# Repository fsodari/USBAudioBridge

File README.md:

# USB Audio Bridge

KiCAD Project for a USB Audio Bridge based on an NXP RT1010

## Requirements

- NXP RT1010
- High Speed USB C connector
- MCU Link compatible SWD header
- 2 PMOD pin headers designed to mate with an Arty A7 development board
    - Route 2 I2S busses through one PMOD. One for input, one for output
    - Route SPI and GPIO through the second PMOD.
- Should be designed for a USB asynchronous audio class device.
- Should use a stable, accurate, 24.576Mhz oscillator for the Audio master clock

## KiCAD Project Requirements
- All erc/drc should pass
- Include 3D models for all parts
- Set up pipelines to generate design files that can be delivered to a PCBA manufacturer

## Using this repository

- `hardware/`: KiCad 10 project (revision v1.0). The schematic is generated from `tools/design.py`; edit that, not the `.kicad_sch` files.
- `docs/reference-manual.md`: developer reference for the RT1010 firmware and the Arty A7 FPGA design (pin map, clocks, boot, I2S/USB/SPI, XDC constraints, errata).
- Fabrication outputs for JLCPCB and PCBWay (Gerbers, drill, BOM, pick-and-place, assembly drawings, schematic PDF):
  - locally: `python3 tools/fab.py` (needs KiCad 10), output in `hardware/build/fab/`
  - on GitHub: the "Fabrication outputs" workflow runs on every push to `main` and uploads both packages as artifacts; pushing a `v*` tag attaches them to a release.

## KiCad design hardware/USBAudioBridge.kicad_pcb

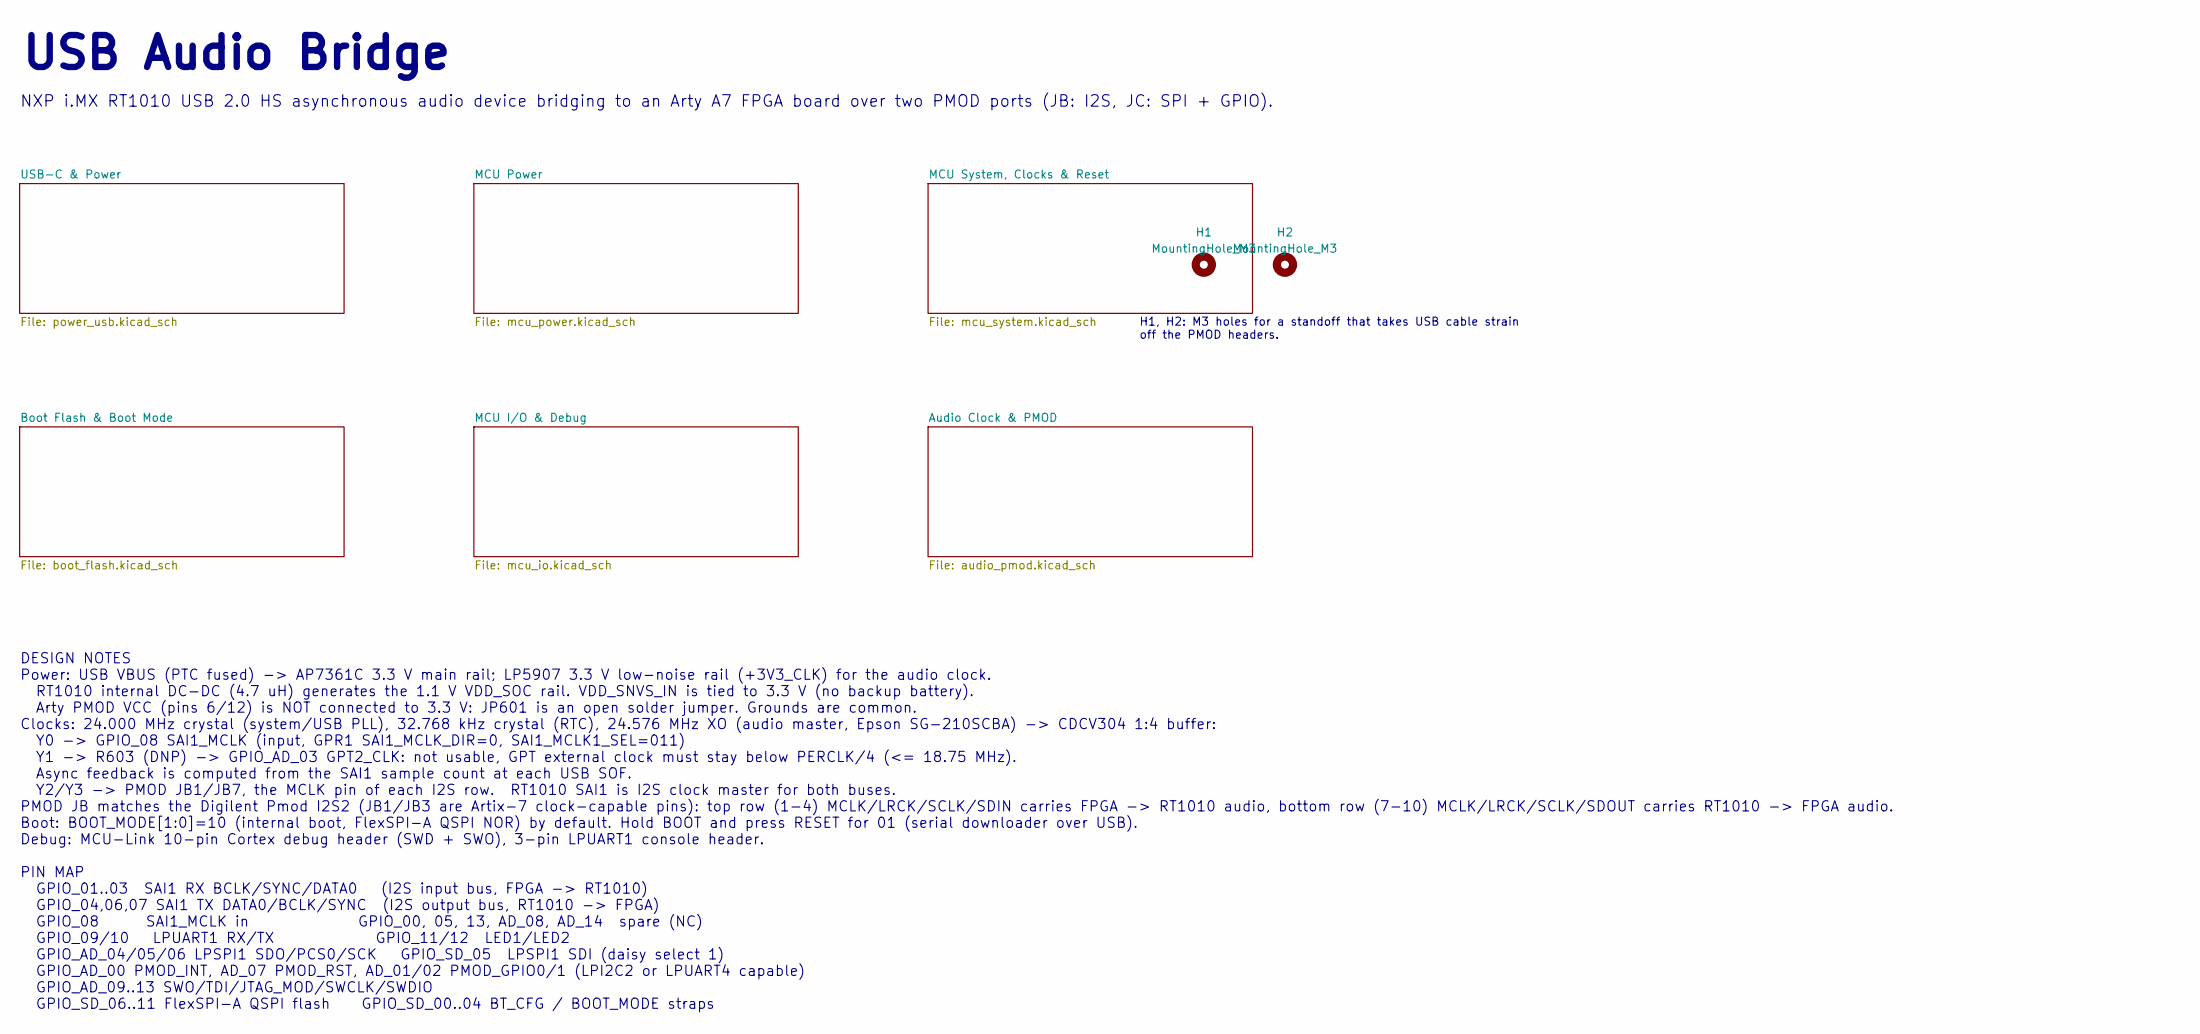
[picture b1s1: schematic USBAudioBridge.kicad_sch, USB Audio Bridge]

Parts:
H1, H2: MountingHole_M3; MountingHole_3.2mm_M3

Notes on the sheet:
USB Audio Bridge
DESIGN NOTES Power: USB VBUS (PTC fused) -> AP7361C 3.3 V main rail; LP5907 3.3 V low-noise rail (+3V3_CLK) for the audio clock. RT1010 internal DC-DC (4.7 uH) generates the 1.1 V VDD_SOC rail. VDD_SNVS_IN is tied to 3.3 V (no backup battery). Arty PMOD VCC (pins 6/12) is NOT connected to 3.3 V: JP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
H1, H2: M3 holes for a standoff that takes USB cable strain off the PMOD headers.
NXP i.MX RT1010 USB 2.0 HS asynchronous audio device bridging to an Arty A7 FPGA board over two PMOD ports (JB: I2S, JC: SPI + GPIO).

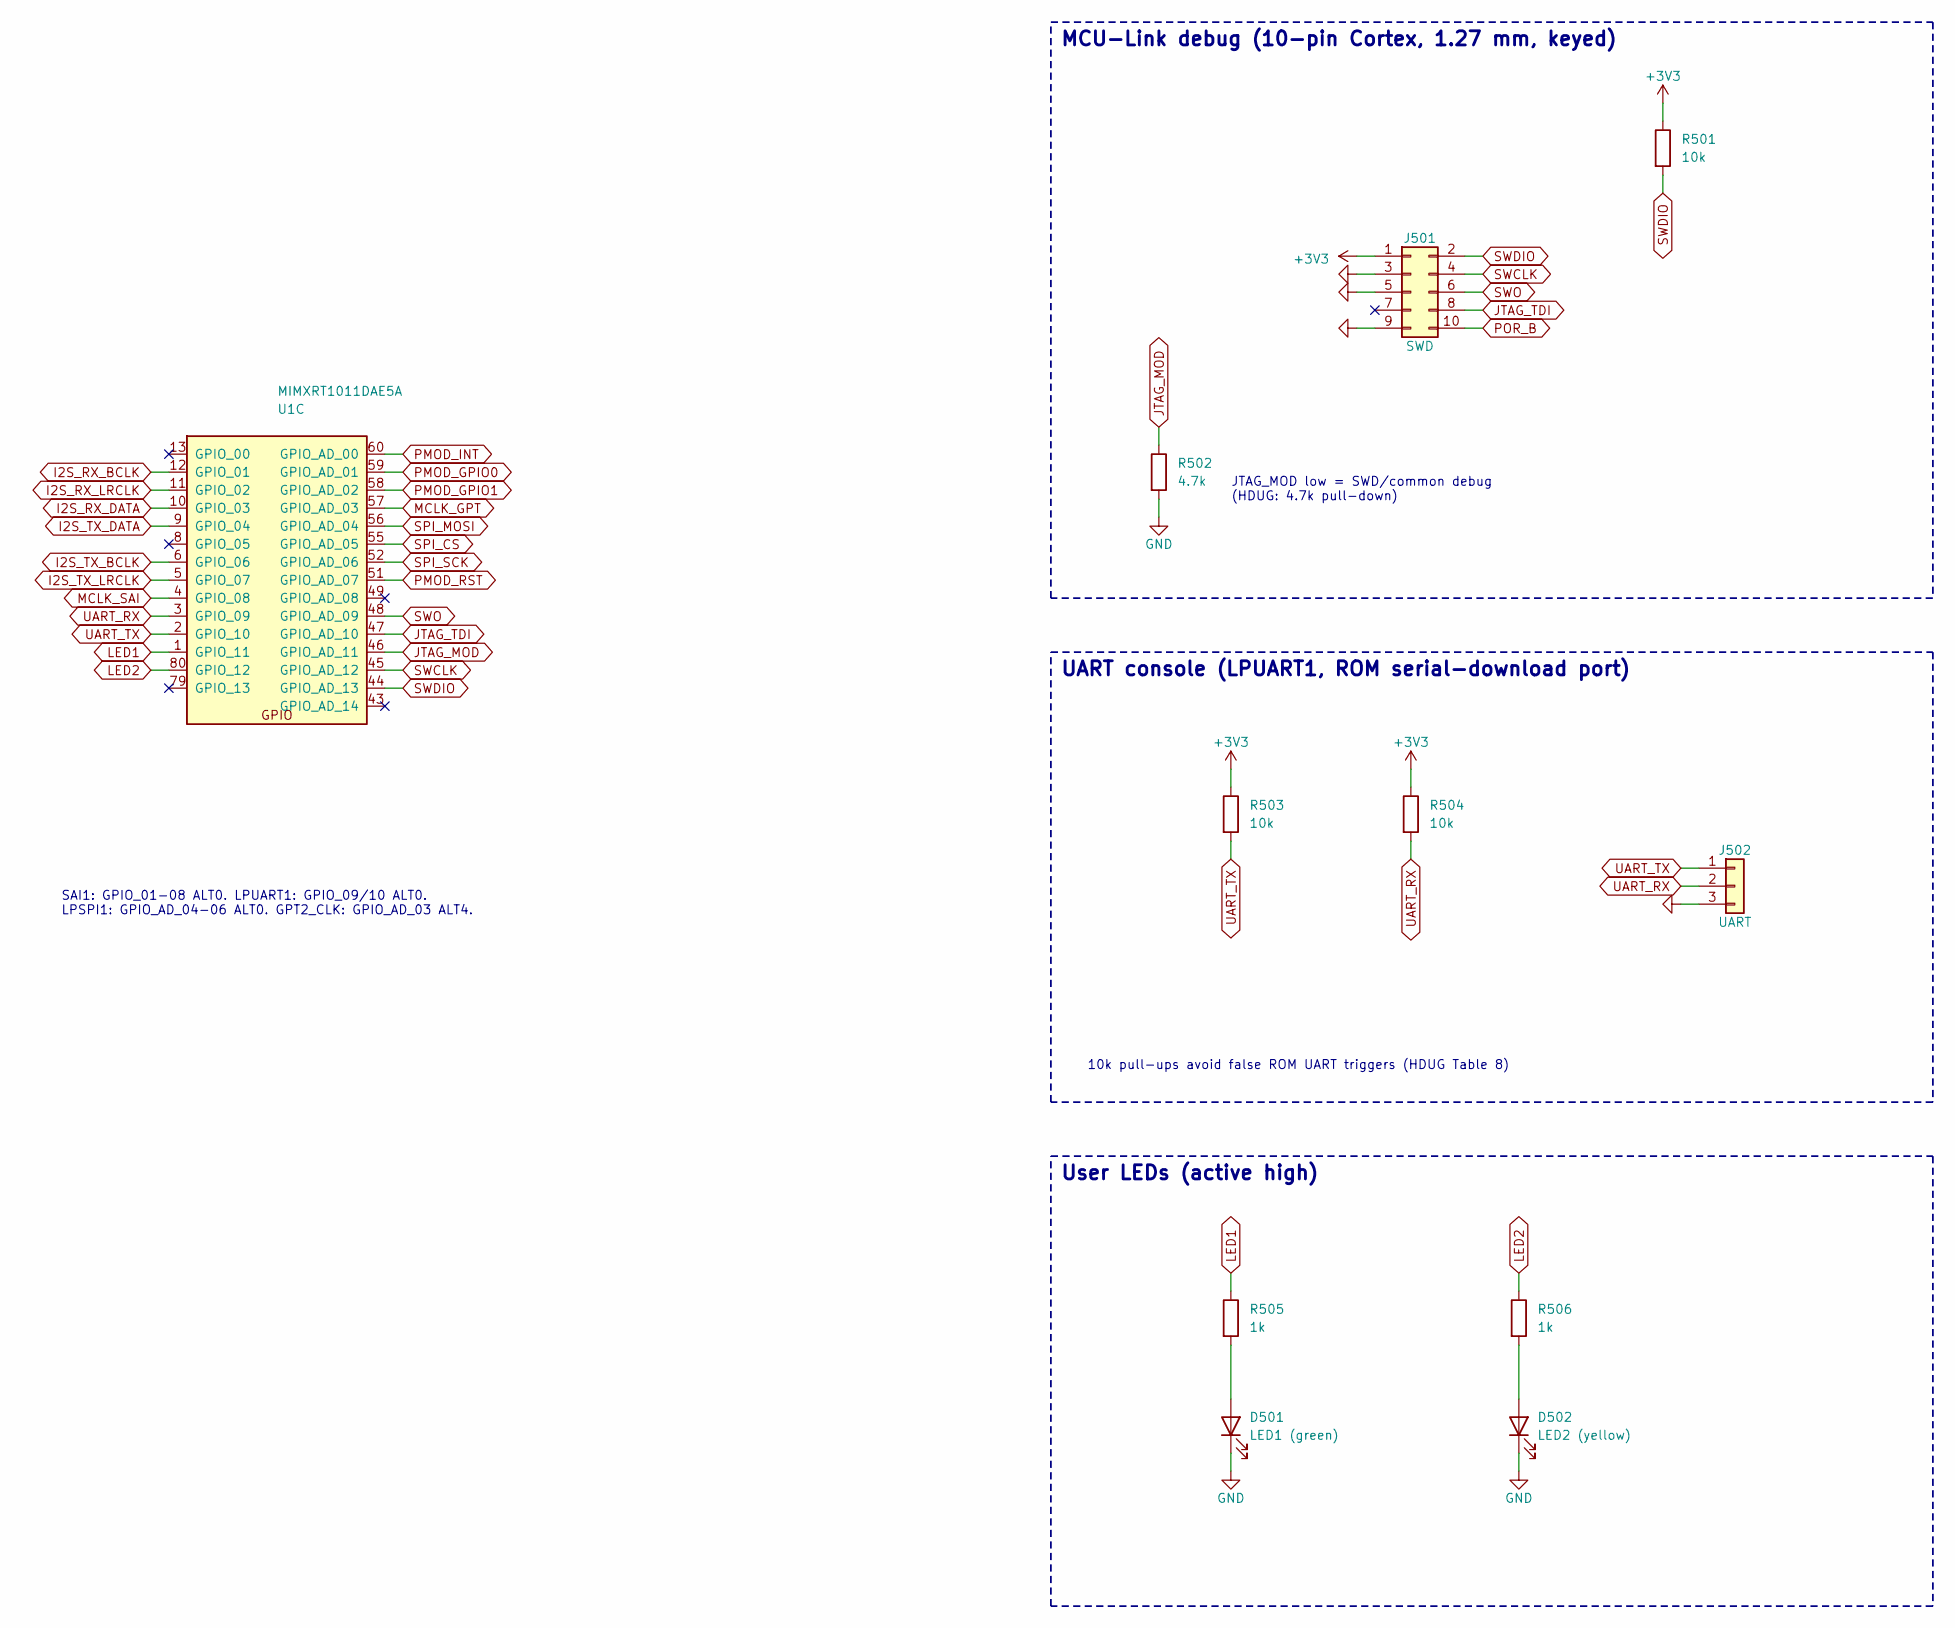
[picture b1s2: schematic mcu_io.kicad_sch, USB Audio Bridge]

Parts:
D501: LED1 (green); LED_0603_1608Metric; MPN KT-0603YG; LCSC C2289
D502: LED2 (yellow); LED_0603_1608Metric; MPN KT-0603Y; LCSC C2287
J501: SWD; Samtec_FTSH-105-01-L-DV-K; MPN FTSH-105-01-L-DV-K; LCSC C5155080
J502: UART; PinHeader_1x03_P2.54mm_Vertical; MPN PZ254V-11-03P; LCSC C2937625
R501, R503, R504: 10k; R_0402_1005Metric; MPN 0402WGF1002TCE; LCSC C25744
R502: 4.7k; R_0402_1005Metric; MPN 0402WGF4701TCE; LCSC C25900
R505, R506: 1k; R_0402_1005Metric; MPN 0402WGF1001TCE; LCSC C11702
U1: MIMXRT1011DAE5A; LQFP-80_12x12mm_P0.5mm; MPN MIMXRT1011DAE5A; LCSC C1575810

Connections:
+3V3: J501.1, R501.1, R503.1, R504.1; also elsewhere on the board
GND: D501.1 (K), D502.1 (K), J501.3, J501.5, J501.9, J502.3, R502.2; also elsewhere on the board
I2S_RX_BCLK: U1.12 (GPIO_01); also elsewhere on the board
I2S_RX_DATA: U1.10 (GPIO_03); also elsewhere on the board
I2S_RX_LRCLK: U1.11 (GPIO_02); also elsewhere on the board
I2S_TX_BCLK: U1.6 (GPIO_06); also elsewhere on the board
I2S_TX_DATA: U1.9 (GPIO_04); also elsewhere on the board
I2S_TX_LRCLK: U1.5 (GPIO_07); also elsewhere on the board
JTAG_MOD: R502.1, U1.46 (GPIO_AD_11)
JTAG_TDI: J501.8, U1.47 (GPIO_AD_10)
LED1: R505.1, U1.1 (GPIO_11)
LED2: R506.1, U1.80 (GPIO_12)
MCLK_GPT: U1.57 (GPIO_AD_03); also elsewhere on the board
MCLK_SAI: U1.4 (GPIO_08); also elsewhere on the board
unnamed: D501.2 (A), R505.2
unnamed: D502.2 (A), R506.2
PMOD_GPIO0: U1.59 (GPIO_AD_01); also elsewhere on the board
PMOD_GPIO1: U1.58 (GPIO_AD_02); also elsewhere on the board
PMOD_INT: U1.60 (GPIO_AD_00); also elsewhere on the board
PMOD_RST: U1.51 (GPIO_AD_07); also elsewhere on the board
POR_B: J501.10; also elsewhere on the board
SPI_CS: U1.55 (GPIO_AD_05); also elsewhere on the board
SPI_MOSI: U1.56 (GPIO_AD_04); also elsewhere on the board
SPI_SCK: U1.52 (GPIO_AD_06); also elsewhere on the board
SWCLK: J501.4, U1.45 (GPIO_AD_12)
SWDIO: J501.2, R501.2, U1.44 (GPIO_AD_13)
SWO: J501.6, U1.48 (GPIO_AD_09)
UART_RX: J502.2, R504.2, U1.3 (GPIO_09)
UART_TX: J502.1, R503.2, U1.2 (GPIO_10)

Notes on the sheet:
10k pull-ups avoid false ROM UART triggers (HDUG Table 8)
UART console (LPUART1, ROM serial-download port)
User LEDs (active high)
SAI1: GPIO_01-08 ALT0. LPUART1: GPIO_09/10 ALT0. LPSPI1: GPIO_AD_04-06 ALT0. GPT2_CLK: GPIO_AD_03 ALT4.
MCU-Link debug (10-pin Cortex, 1.27 mm, keyed)
JTAG_MOD low = SWD/common debug (HDUG: 4.7k pull-down)

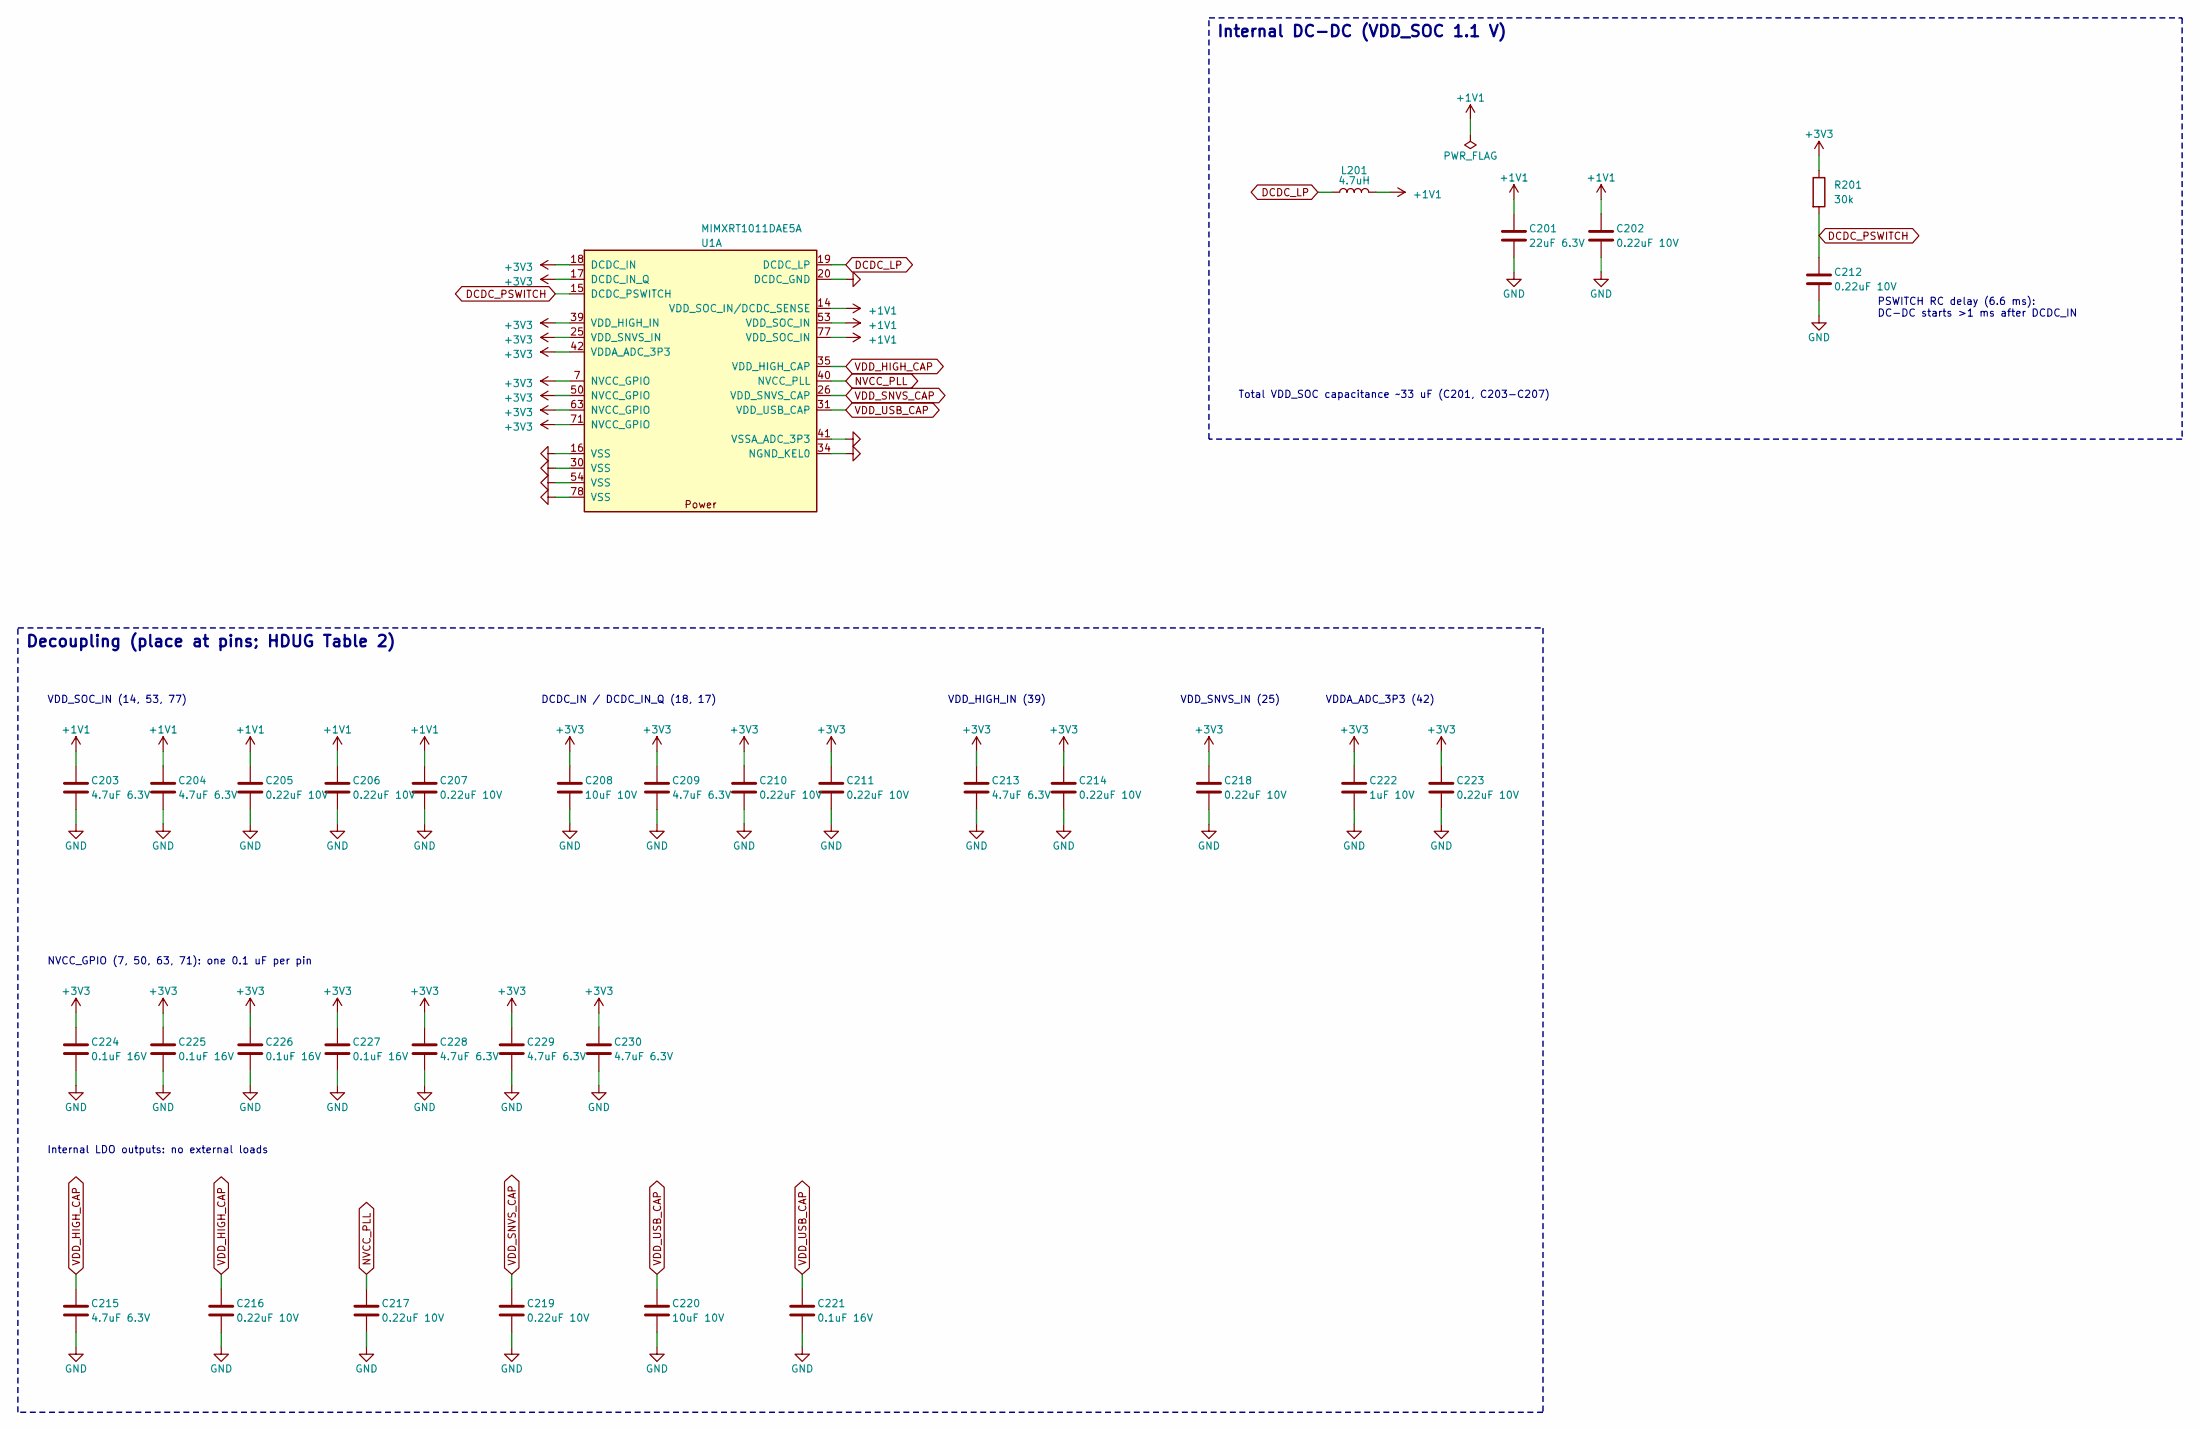
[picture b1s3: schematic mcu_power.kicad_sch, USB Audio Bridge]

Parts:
C201: 22uF 6.3V; C_0805_2012Metric; MPN CL21A226MAQNNNE; LCSC C45783
C202, C205, C206, C207, C210, C211, C212, C214, C216, C217, C218, C219, C223: 0.22uF 10V; C_0402_1005Metric; MPN CL05B224KO5NNNC; LCSC C16772
C203, C204, C209, C213, C215, C228, C229, C230: 4.7uF 6.3V; C_0402_1005Metric; MPN CL05A475MP5NRNC; LCSC C23733
C208, C220: 10uF 10V; C_0603_1608Metric; MPN CL10A106KP8NNNC; LCSC C19702
C221, C224, C225, C226, C227: 0.1uF 16V; C_0402_1005Metric; MPN CL05B104KO5NNNC; LCSC C1525
C222: 1uF 10V; C_0402_1005Metric; MPN CL05A105KA5NQNC; LCSC C52923
L201: 4.7uH; L_Bourns-SRN4018; MPN SRN4018-4R7M; LCSC C780206
R201: 30k; R_0402_1005Metric; MPN 0402WGF3002TCE; LCSC C25776
U1: MIMXRT1011DAE5A; LQFP-80_12x12mm_P0.5mm; MPN MIMXRT1011DAE5A; LCSC C1575810

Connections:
+1V1: C201.1, C202.1, C203.1, C204.1, C205.1, C206.1, C207.1, L201.2, U1.14 (VDD_SOC_IN/DCDC_SENSE), U1.53 (VDD_SOC_IN), U1.77 (VDD_SOC_IN)
+3V3: C208.1, C209.1, C210.1, C211.1, C213.1, C214.1, C218.1, C222.1, C223.1, C224.1, C225.1, C226.1, C227.1, C228.1, C229.1, C230.1, R201.1, U1.7 (NVCC_GPIO), U1.17 (DCDC_IN_Q), U1.18 (DCDC_IN), U1.25 (VDD_SNVS_IN), U1.39 (VDD_HIGH_IN), U1.42 (VDDA_ADC_3P3), U1.50 (NVCC_GPIO), U1.63 (NVCC_GPIO), U1.71 (NVCC_GPIO); also elsewhere on the board
DCDC_LP: L201.1, U1.19 (DCDC_LP)
DCDC_PSWITCH: C212.1, R201.2, U1.15 (DCDC_PSWITCH)
GND: C201.2, C202.2, C203.2, C204.2, C205.2, C206.2, C207.2, C208.2, C209.2, C210.2, C211.2, C212.2, C213.2, C214.2, C215.2, C216.2, C217.2, C218.2, C219.2, C220.2, C221.2, C222.2, C223.2, C224.2, C225.2, C226.2, C227.2, C228.2, C229.2, C230.2, U1.16 (VSS), U1.20 (DCDC_GND), U1.30 (VSS), U1.34 (NGND_KEL0), U1.41 (VSSA_ADC_3P3), U1.54 (VSS), U1.78 (VSS); also elsewhere on the board
NVCC_PLL: C217.1, U1.40 (NVCC_PLL)
VDD_HIGH_CAP: C215.1, C216.1, U1.35 (VDD_HIGH_CAP)
VDD_SNVS_CAP: C219.1, U1.26 (VDD_SNVS_CAP)
VDD_USB_CAP: C220.1, C221.1, U1.31 (VDD_USB_CAP)

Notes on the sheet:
Internal DC-DC (VDD_SOC 1.1 V)
Total VDD_SOC capacitance ~33 uF (C201, C203-C207)
NVCC_GPIO (7, 50, 63, 71): one 0.1 uF per pin
PSWITCH RC delay (6.6 ms): DC-DC starts >1 ms after DCDC_IN
VDD_SNVS_IN (25)
DCDC_IN / DCDC_IN_Q (18, 17)
VDD_SOC_IN (14, 53, 77)
VDD_HIGH_IN (39)
Internal LDO outputs: no external loads
Decoupling (place at pins; HDUG Table 2)
VDDA_ADC_3P3 (42)

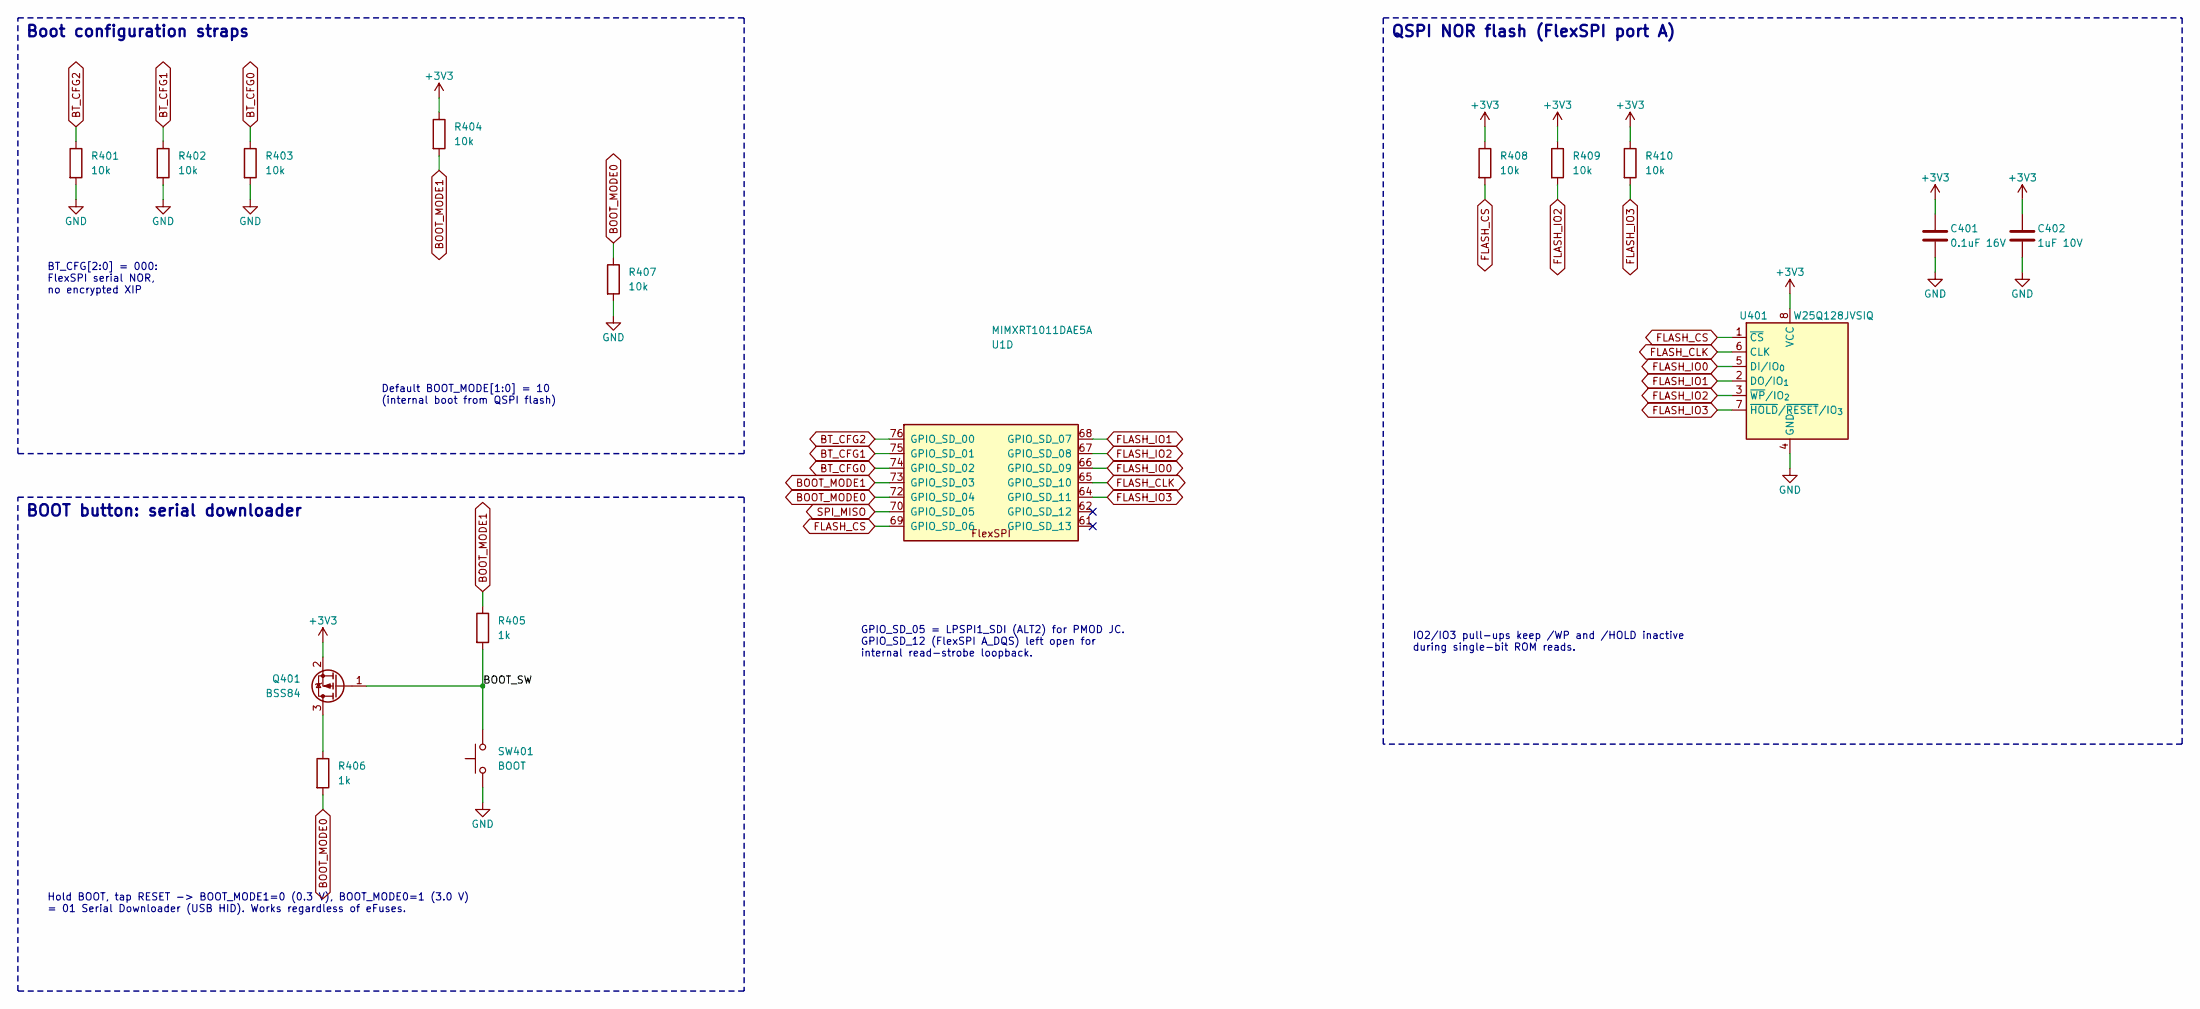
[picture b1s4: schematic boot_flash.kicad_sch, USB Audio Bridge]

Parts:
C401: 0.1uF 16V; C_0402_1005Metric; MPN CL05B104KO5NNNC; LCSC C1525
C402: 1uF 10V; C_0402_1005Metric; MPN CL05A105KA5NQNC; LCSC C52923
Q401: BSS84; SOT-23; MPN BSS84LT1G; LCSC C82079
R401, R402, R403, R404, R407, R408, R409, R410: 10k; R_0402_1005Metric; MPN 0402WGF1002TCE; LCSC C25744
R405, R406: 1k; R_0402_1005Metric; MPN 0402WGF1001TCE; LCSC C11702
SW401: BOOT; SW_SPST_PTS810; MPN PTS810SJG250SMTRLFS; LCSC C221895
U1: MIMXRT1011DAE5A; LQFP-80_12x12mm_P0.5mm; MPN MIMXRT1011DAE5A; LCSC C1575810
U401: W25Q128JVSIQ; SOIC-8_5.3x5.3mm_P1.27mm; MPN W25Q128JVSIQ; LCSC C97521

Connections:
+3V3: C401.1, C402.1, Q401.2 (S), R404.1, R408.1, R409.1, R410.1, U401.8 (VCC); also elsewhere on the board
/Boot Flash & Boot Mode/BOOT_SW: Q401.1 (G), R405.2, SW401.2
BOOT_MODE0: R406.2, R407.1, U1.72 (GPIO_SD_04)
BOOT_MODE1: R404.2, R405.1, U1.73 (GPIO_SD_03)
BT_CFG0: R403.1, U1.74 (GPIO_SD_02)
BT_CFG1: R402.1, U1.75 (GPIO_SD_01)
BT_CFG2: R401.1, U1.76 (GPIO_SD_00)
FLASH_CLK: U1.65 (GPIO_SD_10), U401.6 (CLK)
FLASH_CS: R408.2, U1.69 (GPIO_SD_06), U401.1 (~CS)
FLASH_IO0: U1.66 (GPIO_SD_09), U401.5 (DI/IO_{0})
FLASH_IO1: U1.68 (GPIO_SD_07), U401.2 (DO/IO_{1})
FLASH_IO2: R409.2, U1.67 (GPIO_SD_08), U401.3 (~WP/IO_{2})
FLASH_IO3: R410.2, U1.64 (GPIO_SD_11), U401.7 (~HOLD/~RESET/IO_{3})
GND: C401.2, C402.2, R401.2, R402.2, R403.2, R407.2, SW401.1, U401.4 (GND); also elsewhere on the board
unnamed: Q401.3 (D), R406.1
SPI_MISO: U1.70 (GPIO_SD_05); also elsewhere on the board

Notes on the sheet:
BT_CFG[2:0] = 000: FlexSPI serial NOR, no encrypted XIP
GPIO_SD_05 = LPSPI1_SDI (ALT2) for PMOD JC. GPIO_SD_12 (FlexSPI A_DQS) left open for internal read-strobe loopback.
QSPI NOR flash (FlexSPI port A)
Boot configuration straps
Default BOOT_MODE[1:0] = 10 (internal boot from QSPI flash)
BOOT button: serial downloader
IO2/IO3 pull-ups keep /WP and /HOLD inactive during single-bit ROM reads.
Hold BOOT, tap RESET -> BOOT_MODE1=0 (0.3 V), BOOT_MODE0=1 (3.0 V) = 01 Serial Downloader (USB HID). Works regardless of eFuses.

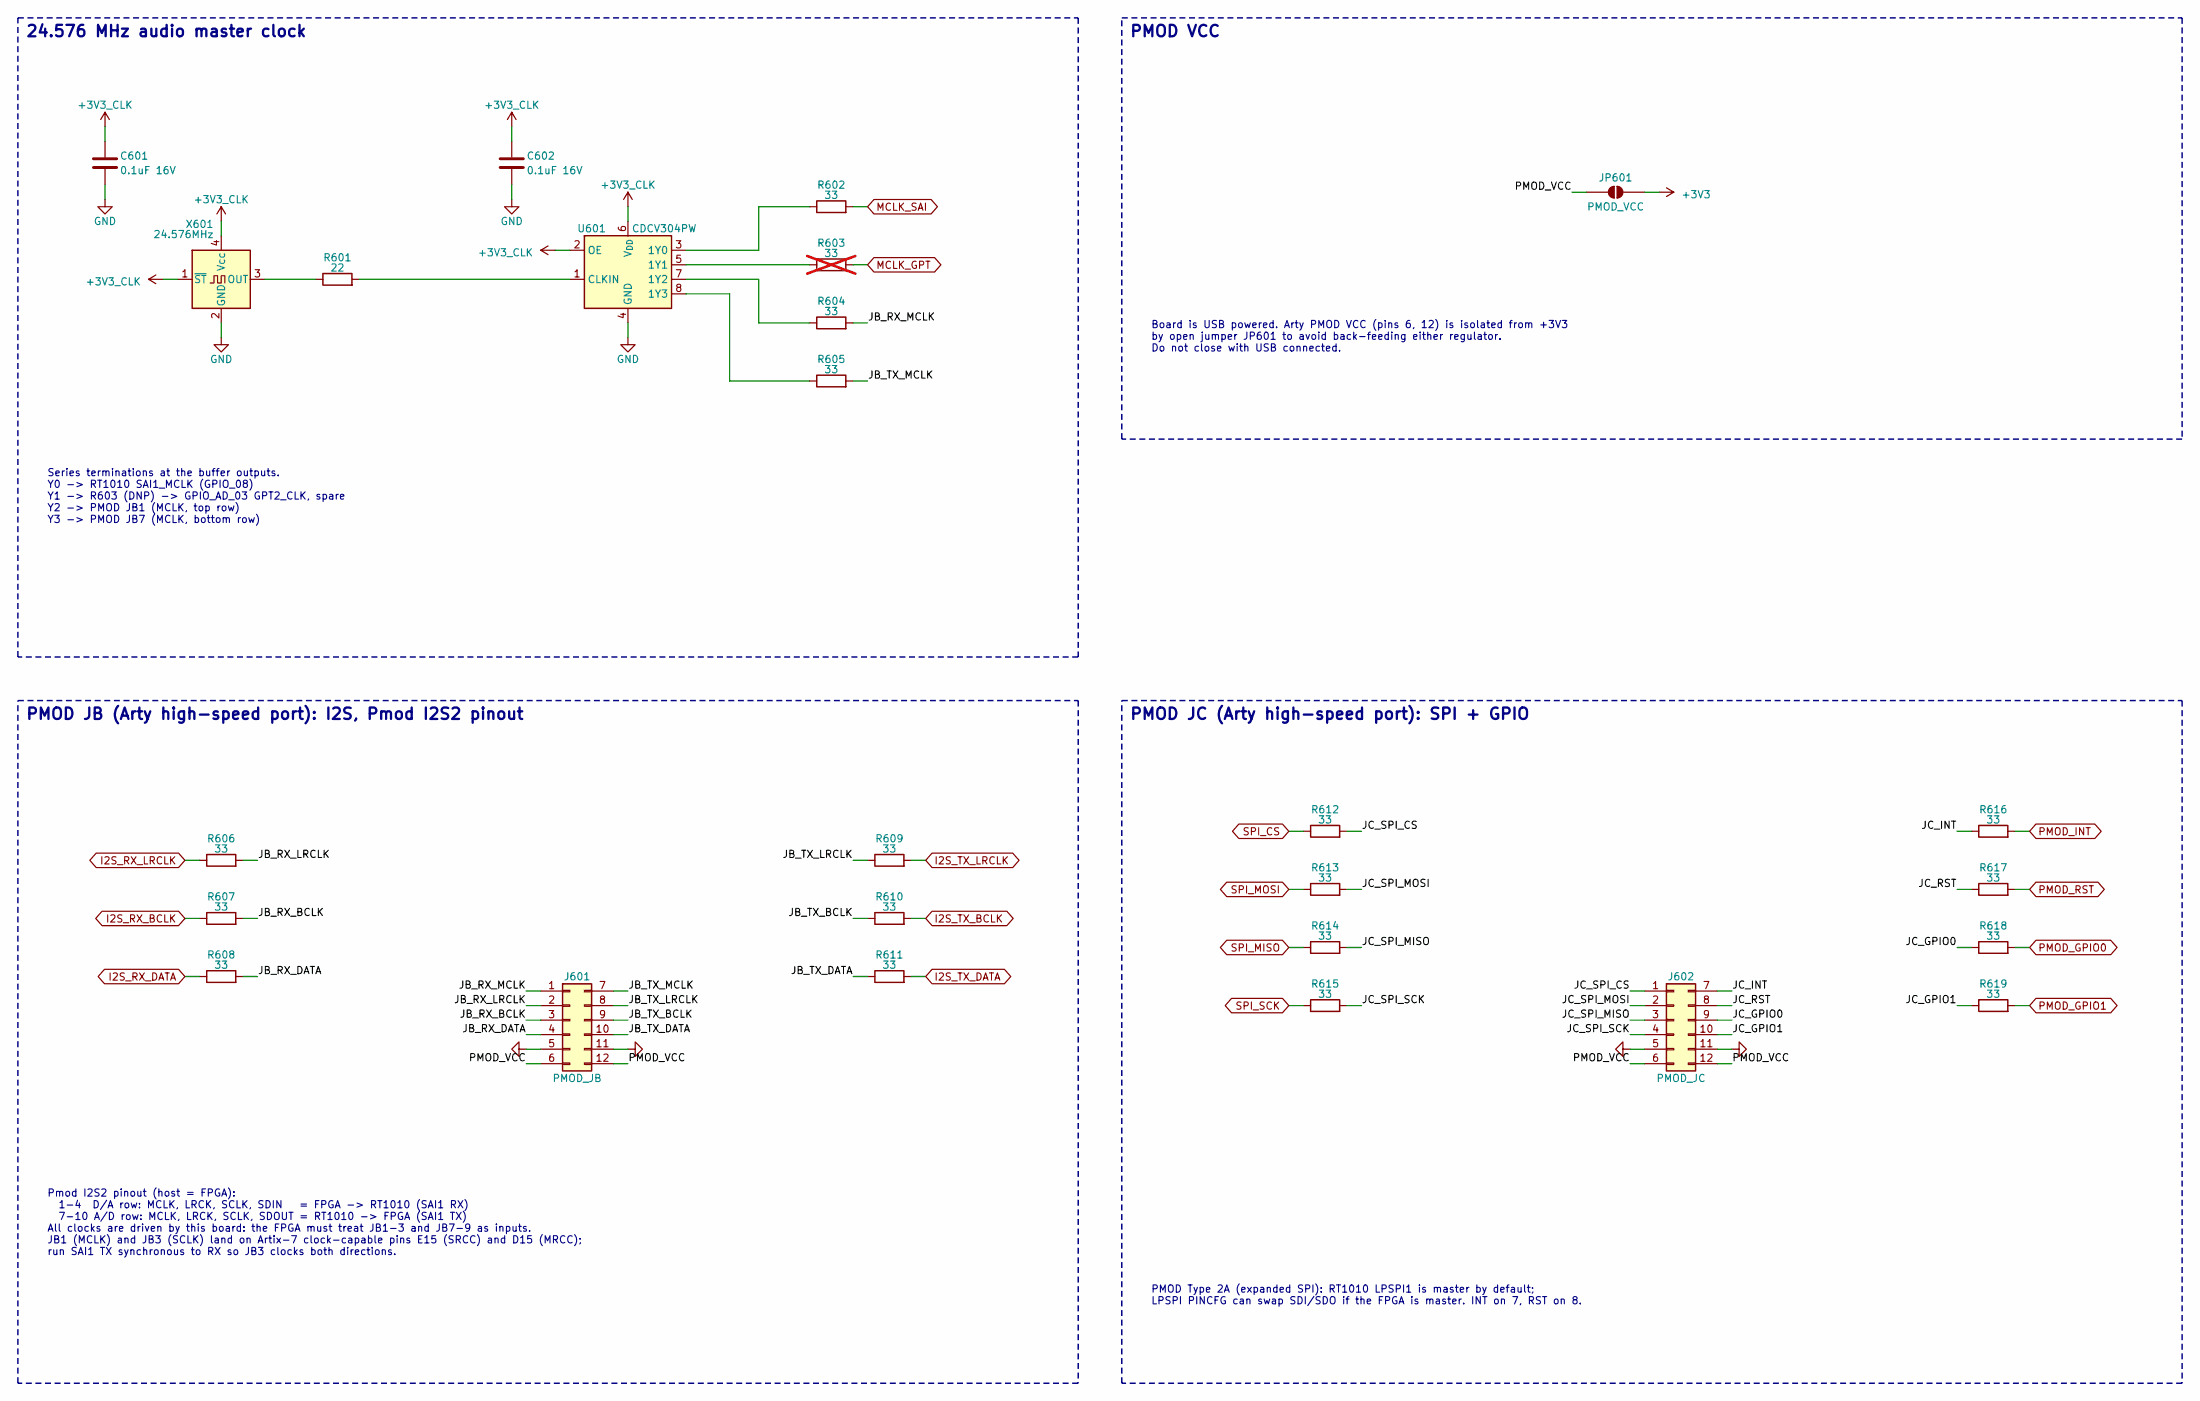
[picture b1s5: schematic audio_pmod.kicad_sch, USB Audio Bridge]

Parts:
C601, C602: 0.1uF 16V; C_0402_1005Metric; MPN CL05B104KO5NNNC; LCSC C1525
J601: PMOD_JB; PMOD_Peripheral_2x06_P2.54mm_Horizontal; MPN PZ254R-12-12P; LCSC C492434
J602: PMOD_JC; PMOD_Peripheral_2x06_P2.54mm_Horizontal; MPN PZ254R-12-12P; LCSC C492434
JP601: PMOD_VCC; SolderJumper-2_P1.3mm_Open_RoundedPad1.0x1.5mm
R601: 22; R_0402_1005Metric; MPN 0402WGF220JTCE; LCSC C25092
R602, R604, R605, R606, R607, R608, R609, R610, R611, R612, R613, R614, R615, R616, R617, R618, R619: 33; R_0402_1005Metric; MPN 0402WGF330JTCE; LCSC C25105
R603: 33; R_0402_1005Metric; MPN 0402WGF330JTCE; LCSC C25105; not fitted
U601: CDCV304PW; TSSOP-8_4.4x3mm_P0.65mm; MPN CDCV304PWR; LCSC C105237
X601: 24.576MHz; Oscillator_SMD_SeikoEpson_SG210-4Pin_2.5x2.0mm; MPN X1G004591A052; LCSC C5154204

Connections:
+3V3: JP601.2 (B); also elsewhere on the board
+3V3_CLK: C601.1, C602.1, U601.2 (OE), U601.6 (V_{DD}), X601.1 (~ST), X601.4 (Vcc); also elsewhere on the board
/Audio Clock & PMOD/JB_RX_BCLK: J601.3, R607.2
/Audio Clock & PMOD/JB_RX_DATA: J601.4, R608.2
/Audio Clock & PMOD/JB_RX_LRCLK: J601.2, R606.2
/Audio Clock & PMOD/JB_RX_MCLK: J601.1, R604.2
/Audio Clock & PMOD/JB_TX_BCLK: J601.9, R610.1
/Audio Clock & PMOD/JB_TX_DATA: J601.10, R611.1
/Audio Clock & PMOD/JB_TX_LRCLK: J601.8, R609.1
/Audio Clock & PMOD/JB_TX_MCLK: J601.7, R605.2
/Audio Clock & PMOD/JC_GPIO0: J602.9, R618.1
/Audio Clock & PMOD/JC_GPIO1: J602.10, R619.1
/Audio Clock & PMOD/JC_INT: J602.7, R616.1
/Audio Clock & PMOD/JC_RST: J602.8, R617.1
/Audio Clock & PMOD/JC_SPI_CS: J602.1, R612.2
/Audio Clock & PMOD/JC_SPI_MISO: J602.3, R614.2
/Audio Clock & PMOD/JC_SPI_MOSI: J602.2, R613.2
/Audio Clock & PMOD/JC_SPI_SCK: J602.4, R615.2
/Audio Clock & PMOD/PMOD_VCC: J601.6, J601.12, J602.6, J602.12, JP601.1 (A)
GND: C601.2, C602.2, J601.5, J601.11, J602.5, J602.11, U601.4 (GND), X601.2 (GND); also elsewhere on the board
I2S_RX_BCLK: R607.1; also elsewhere on the board
I2S_RX_DATA: R608.1; also elsewhere on the board
I2S_RX_LRCLK: R606.1; also elsewhere on the board
I2S_TX_BCLK: R610.2; also elsewhere on the board
I2S_TX_DATA: R611.2; also elsewhere on the board
I2S_TX_LRCLK: R609.2; also elsewhere on the board
MCLK_GPT: R603.2; also elsewhere on the board
MCLK_SAI: R602.2; also elsewhere on the board
unnamed: R602.1, U601.3 (1Y0)
unnamed: R603.1, U601.5 (1Y1)
unnamed: R604.1, U601.7 (1Y2)
unnamed: R605.1, U601.8 (1Y3)
unnamed: R601.2, U601.1 (CLKIN)
unnamed: R601.1, X601.3 (OUT)
PMOD_GPIO0: R618.2; also elsewhere on the board
PMOD_GPIO1: R619.2; also elsewhere on the board
PMOD_INT: R616.2; also elsewhere on the board
PMOD_RST: R617.2; also elsewhere on the board
SPI_CS: R612.1; also elsewhere on the board
SPI_MISO: R614.1; also elsewhere on the board
SPI_MOSI: R613.1; also elsewhere on the board
SPI_SCK: R615.1; also elsewhere on the board

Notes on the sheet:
24.576 MHz audio master clock
PMOD JC (Arty high-speed port): SPI + GPIO
PMOD JB (Arty high-speed port): I2S, Pmod I2S2 pinout
Board is USB powered. Arty PMOD VCC (pins 6, 12) is isolated from +3V3 by open jumper JP601 to avoid back-feeding either regulator. Do not close with USB connected.
Pmod I2S2 pinout (host = FPGA): 1-4 D/A row: MCLK, LRCK, SCLK, SDIN = FPGA -> RT1010 (SAI1 RX) 7-10 A/D row: MCLK, LRCK, SCLK, SDOUT = RT1010 -> FPGA (SAI1 TX) All clocks are driven by this board: the FPGA must treat JB1-3 and JB7-9 as inputs. JB1 (MCLK) and JB3 (SCLK) land on Artix-7 clock-capable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
PMOD Type 2A (expanded SPI): RT1010 LPSPI1 is master by default; LPSPI PINCFG can swap SDI/SDO if the FPGA is master. INT on 7, RST on 8.
Series terminations at the buffer outputs. Y0 -> RT1010 SAI1_MCLK (GPIO_08) Y1 -> R603 (DNP) -> GPIO_AD_03 GPT2_CLK, spare Y2 -> PMOD JB1 (MCLK, top row) Y3 -> PMOD JB7 (MCLK, bottom row)
PMOD VCC
